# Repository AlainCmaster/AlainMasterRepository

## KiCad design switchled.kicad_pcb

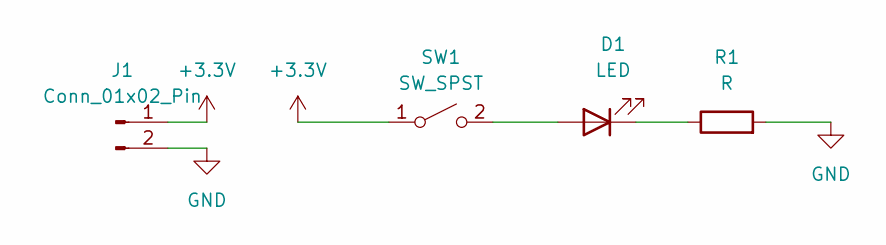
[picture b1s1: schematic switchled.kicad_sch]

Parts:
D1: LED; LED_D3.0mm_Horizontal_O6.35mm_Z10.0mm
J1: Conn_01x02_Pin; PinHeader_1x02_P2.54mm_Vertical
R1: R; R_0201_0603Metric
SW1: SW_SPST; SW_SPST_CK_RS282G05A3

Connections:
+3.3V: J1.1, SW1.1 (A)
GND: J1.2, R1.2
unnamed: D1.2 (A), SW1.2 (B)
unnamed: D1.1 (K), R1.1

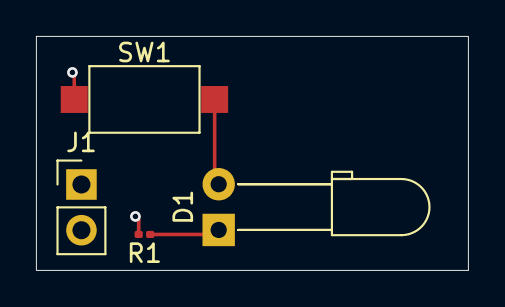
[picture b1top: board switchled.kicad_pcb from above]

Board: 4 copper layers, 24.0 x 13.0 mm, 4 parts (0 on the bottom side), 4 nets.

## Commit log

2024-09-19 archivo subido
2024-09-21 Alain
